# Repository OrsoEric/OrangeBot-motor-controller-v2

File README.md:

# OrangeBot-motor-controller-v2
Motor controller for OrangeBot Robot  
-VNH7040 Motor Driver  
-GD32VF103 Microcontroller  
-IG32E-05K Motor  

# Blog Entry  
https://orangebotpiwars2021.blogspot.com/2021/03/2021-03-20-orangebot-motor-controller.html

# Schematics  

# Test bench

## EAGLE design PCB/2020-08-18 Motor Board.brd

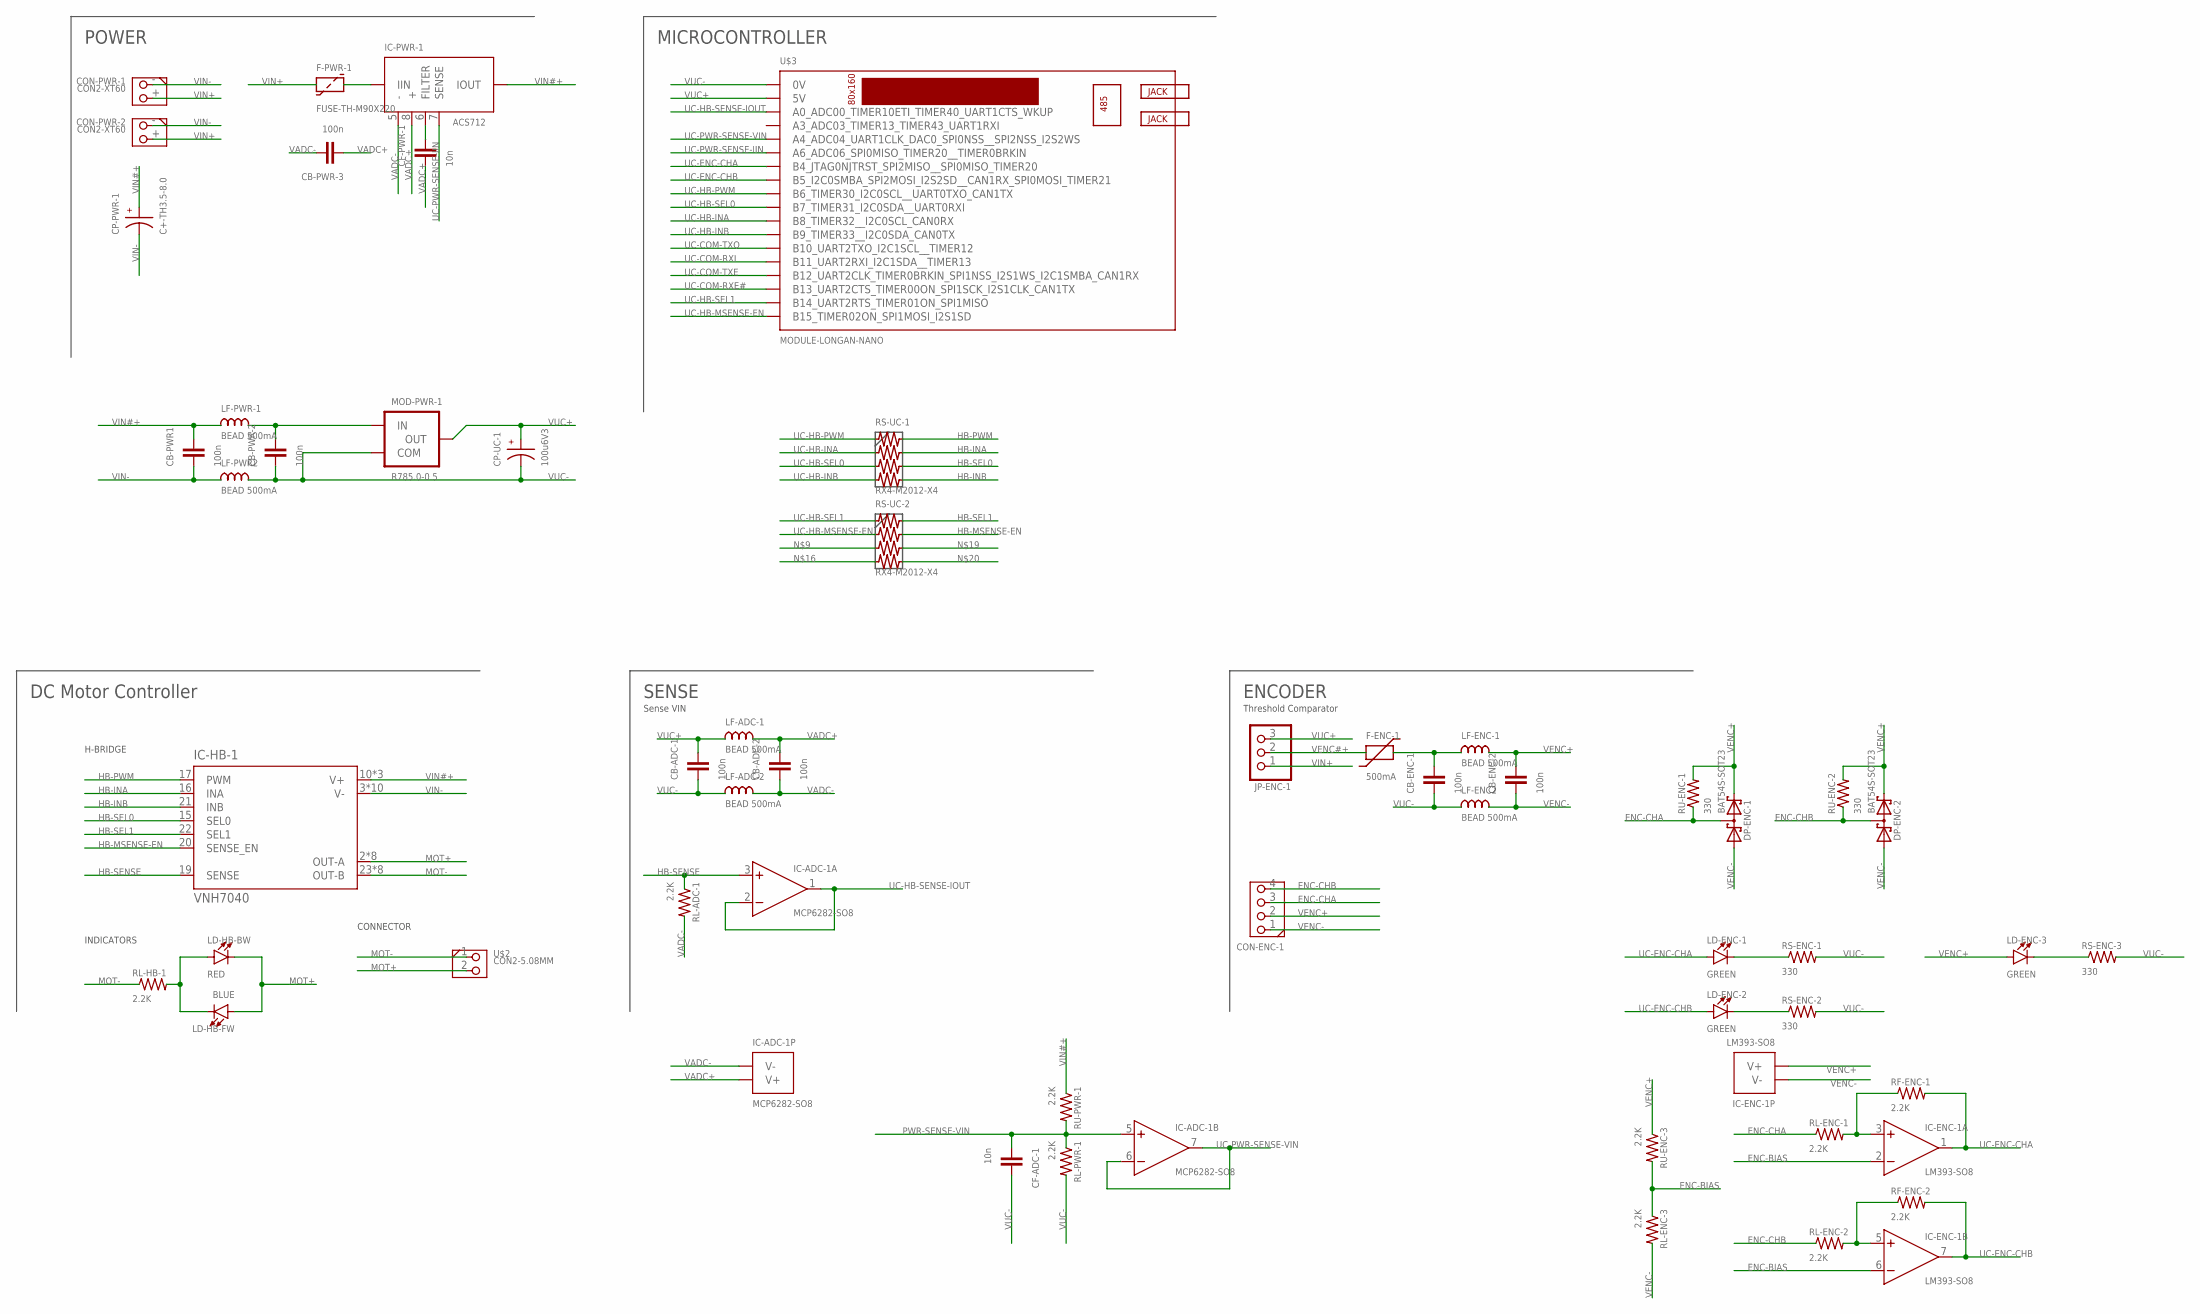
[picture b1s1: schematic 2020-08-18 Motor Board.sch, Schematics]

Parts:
CB-ADC-1, CB-ADC-2: 100n; SMD-M2012
CB-ENC-1, CB-ENC-2: 100n; SMD-M2012
CB-PWR1: 100n; SMD-M2012
CB-PWR-2, CB-PWR-3: 100n; SMD-M2012
CF-ADC-1: 10n; SMD-M2012
CF-PWR-1: 10n; SMD-M2012
CON-ENC-1: CON4
CON-PWR-1, CON-PWR-2: CON2-XT60; AMASS_XT60-M
CP-PWR-1: C+-TH3.5-8.0; TH-BARREL-3M5-8M0
CP-UC-1: 100u6V3; TH-BARREL-2M54-6M0
DP-ENC-1, DP-ENC-2: BAT54S-SOT23; SOT23
F-ENC-1: 500mA; SMD-M2012
F-PWR-1: FUSE-TH-M90X220; TH-BOX-MM9X22
IC-ADC-1: MCP6282-SO8; SO8
IC-ENC-1: LM393-SO8; SO8
IC-HB-1: VNH7040; SSO-36-TP
IC-PWR-1: ACS712; SO8
JP-ENC-1: PINHD-1X3; 1X03
LD-ENC-1, LD-ENC-2, LD-ENC-3: GREEN; SMD-M2012-POL
LD-HB-BW: RED; SMD-M2012-POL
LD-HB-FW: BLUE; SMD-M2012-POL
LF-ADC-1, LF-ADC-2: BEAD 500mA; SMD-M2012
LF-ENC2: BEAD 500mA; SMD-M2012
LF-ENC-1: BEAD 500mA; SMD-M2012
LF-PWR2: BEAD 500mA; SMD-M2012
LF-PWR-1: BEAD 500mA; SMD-M2012
MOD-PWR-1: R785.0-0.5; CUSTOM_SIP3_PIN
RF-ENC-1, RF-ENC-2: 2.2K; SMD-M2012
RL-ADC-1: 2.2K; SMD-M2012
RL-ENC-1, RL-ENC-2, RL-ENC-3: 2.2K; SMD-M2012
RL-HB-1: 2.2K; SMD-M2012
RL-PWR-1: 2.2K; SMD-M2012
RS-ENC-1, RS-ENC-2, RS-ENC-3: 330; SMD-M2012
RS-UC-1, RS-UC-2: RX4-M2012-X4; SMD-M2012-X4
RU-ENC-1, RU-ENC-2: 330; SMD-M2012
RU-ENC-3: 2.2K; SMD-M2012
RU-PWR-1: 2.2K; SMD-M2012
U$2: CON2-5.08MM; CON2-508
U$3: MODULE-LONGAN-NANO

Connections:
ENC-BIAS: IC-ENC-1.2 (-IN), IC-ENC-1.6 (-IN), RL-ENC-3.1, RU-ENC-3.2
ENC-CHA: CON-ENC-1.3, DP-ENC-1.3 (C1A2), RL-ENC-1.1, RU-ENC-1.1
ENC-CHB: CON-ENC-1.4, DP-ENC-2.3 (C1A2), RL-ENC-2.1, RU-ENC-2.1
HB-INA: IC-HB-1.16 (INA), RS-UC-1.2B
HB-INB: IC-HB-1.21 (INB), RS-UC-1.4B
HB-MSENSE-EN: IC-HB-1.20 (SENSE_EN), RS-UC-2.2B
HB-PWM: IC-HB-1.17 (PWM), RS-UC-1.1B
HB-SEL0: IC-HB-1.15 (SEL0), RS-UC-1.3B
HB-SEL1: IC-HB-1.22 (SEL1), RS-UC-2.1B
HB-SENSE: IC-ADC-1.3 (+IN), IC-HB-1.19 (SENSE), RL-ADC-1.1
MOT+: IC-HB-1.2 (OUT-A), IC-HB-1.8 (OUT-A), IC-HB-1.9 (OUT-A), IC-HB-1.11 (OUT-A), IC-HB-1.12 (OUT-A), IC-HB-1.13 (OUT-A), IC-HB-1.14 (OUT-A), IC-HB-1.PAD2 (OUT-A), LD-HB-BW.-, LD-HB-FW.+, U$2.2
MOT-: IC-HB-1.23 (OUT-B), IC-HB-1.24 (OUT-B), IC-HB-1.25 (OUT-B), IC-HB-1.26 (OUT-B), IC-HB-1.28 (OUT-B), IC-HB-1.29 (OUT-B), IC-HB-1.35 (OUT-B), IC-HB-1.PAD3 (OUT-B), RL-HB-1.1, U$2.1
unnamed: LD-HB-BW.+, LD-HB-FW.-, RL-HB-1.2
unnamed: CF-PWR-1.2, IC-PWR-1.6 (FILTER)
unnamed: F-PWR-1.2, IC-PWR-1.1 (IIN), IC-PWR-1.2 (IIN)
unnamed: IC-ENC-1.3 (+IN), RF-ENC-1.1, RL-ENC-1.2
unnamed: LD-ENC-2.-, RS-ENC-2.1
unnamed: IC-ENC-1.5 (+IN), RF-ENC-2.1, RL-ENC-2.2
unnamed: LD-ENC-1.-, RS-ENC-1.1
unnamed: CB-PWR-2.2, LF-PWR-1.2, MOD-PWR-1.VIN (IN)
unnamed: CB-ENC-1.2, F-ENC-1.2, LF-ENC-1.1
unnamed: LD-ENC-3.-, RS-ENC-3.1
PWR-SENSE-VIN: CF-ADC-1.1, IC-ADC-1.5 (+IN), RL-PWR-1.1, RU-PWR-1.2
UC-COM-RXE#: U$3.B13 (B13_UART2CTS_TIMER00ON_SPI1SCK_I2S1CLK_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)
UC-COM-RXI: U$3.B11 (B11_UART2RXI_I2C1SDA__TIMER13)
UC-COM-TXE: U$3.B12 (B12_UART2CLK_TIMER0BRKIN_SPI1NSS_I2S1WS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)
UC-COM-TXO: U$3.B10 (B10_UART2TXO_I2C1SCL__TIMER12)
UC-ENC-CHA: IC-ENC-1.1 (OUT), LD-ENC-1.+, RF-ENC-1.2, U$3.B4 (B4_JTAG0NJTRST_SPI2MISO__SPI0MISO_TIMER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)
UC-ENC-CHB: IC-ENC-1.7 (OUT), LD-ENC-2.+, RF-ENC-2.2, U$3.B5 (B5_I2C0SMBA_SPI2MOSI_I2S2SD__CAN1RX_SPI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)
UC-HB-INA: RS-UC-1.2A, U$3.B8 (B8_TIMER32__I2C0SCL_CAN0RX)
UC-HB-INB: RS-UC-1.4A, U$3.B9 (B9_TIMER33__I2C0SDA_CAN0TX)
UC-HB-MSENSE-EN: RS-UC-2.2A, U$3.B15 (B15_TIMER02ON_SPI1MOSI_I2S1SD)
UC-HB-PWM: RS-UC-1.1A, U$3.B6 (B6_TIMER30_I2C0SCL__UART0TXO_CAN1TX)
UC-HB-SEL0: RS-UC-1.3A, U$3.B7 (B7_TIMER31_I2C0SDA__UART0RXI)
UC-HB-SEL1: RS-UC-2.1A, U$3.B14 (B14_UART2RTS_TIMER01ON_SPI1MISO)
UC-HB-SENSE-IOUT: IC-ADC-1.1 (OUT), IC-ADC-1.2 (-IN), U$3.A0 (A0_ADC00_TIMER10ETI_TIMER40_UART1CTS_WK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)
UC-PWR-SENSE-IIN: IC-PWR-1.7 (SENSE), U$3.A6 (A6_ADC06_SPI0MISO_TIMER20__TIMER0BRKIN)
UC-PWR-SENSE-VIN: IC-ADC-1.6 (-IN), IC-ADC-1.7 (OUT), U$3.A4 (A4_ADC04_UART1CLK_DAC0_SPI0NSS__SPI2NSS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)
VADC+: CB-ADC-2.2, CB-PWR-3.1, CF-PWR-1.1, IC-ADC-1.8 (V+), IC-PWR-1.8 (+), LF-ADC-1.2
VADC-: CB-ADC-2.1, CB-PWR-3.2, IC-ADC-1.4 (V-), IC-PWR-1.5 (-), LF-ADC-2.2, RL-ADC-1.2
VENC#+: F-ENC-1.1, JP-ENC-1.2
VENC+: CB-ENC-2.2, CON-ENC-1.2, DP-ENC-1.2 (C2), DP-ENC-2.2 (C2), IC-ENC-1.8 (V+), LD-ENC-3.+, LF-ENC-1.2, RU-ENC-1.2, RU-ENC-2.2, RU-ENC-3.1
VENC-: CB-ENC-2.1, CON-ENC-1.1, DP-ENC-1.1 (A1), DP-ENC-2.1 (A1), IC-ENC-1.4 (V-), LF-ENC2.2, RL-ENC-3.2
VIN#+: CB-PWR1.2, CP-PWR-1.+, IC-HB-1.10 (V+), IC-HB-1.27 (V+), IC-HB-1.PAD1 (V+), IC-PWR-1.3 (IOUT), IC-PWR-1.4 (IOUT), LF-PWR-1.1, RU-PWR-1.1
VIN+: CON-PWR-1.+ (2), CON-PWR-2.+ (2), F-PWR-1.1, JP-ENC-1.1
VIN-: CB-PWR1.1, CON-PWR-1.- (1), CON-PWR-2.- (1), CP-PWR-1.-, IC-HB-1.3 (V-), IC-HB-1.4 (V-), IC-HB-1.5 (V-), IC-HB-1.6 (V-), IC-HB-1.7 (V-), IC-HB-1.30 (V-), IC-HB-1.31 (V-), IC-HB-1.32 (V-), IC-HB-1.33 (V-), IC-HB-1.34 (V-), LF-PWR2.1
VUC+: CB-ADC-1.2, CP-UC-1.+, JP-ENC-1.3, LF-ADC-1.1, MOD-PWR-1.OUT, U$3.5V
VUC-: CB-ADC-1.1, CB-ENC-1.1, CB-PWR-2.1, CF-ADC-1.2, CP-UC-1.-, LF-ADC-2.1, LF-ENC2.1, LF-PWR2.2, MOD-PWR-1.COM, RL-PWR-1.2, RS-ENC-1.2, RS-ENC-2.2, RS-ENC-3.2, U$3.0V

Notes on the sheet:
POWER
MICROCONTROLLER
DC Motor Controller
ENCODER
SENSE
H-BRIDGE
INDICATORS
CONNECTOR
Threshold Comparator
Sense VIN

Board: 2 copper layers, 54 parts (16 on the bottom side), 44 nets, no tracks yet.

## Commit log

2021-03-20 VNH7040: Operational | Encoder: Operational |
2021-03-20 Datasheet
2021-03-20 2021-03-20 Acquisition of VNH7040 Current Sense pin
2021-03-20 2021-03-20 Schematics
2021-03-20 Update README.md
    Readme
2021-03-20 Add files via upload
    Media
2021-05-16 fixes 16bit PID. Now motor is closed in position
2021-05-16 removes PID32
2021-08-13 changes repository structure.
2021-08-13 fixes reference to breadboard images in readme.
2021-08-13 adds initial placement for PCB schematics and board.
2021-08-13 adds architecture.
2021-08-22 updates schematics, dimensions and placement.
